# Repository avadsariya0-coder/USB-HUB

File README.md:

# USB HUB
Custom 4-port USB-C HUB
___________________________________________________________________________________________________________________________________________________________________________

## Overview

 USB HUB is a custom designed USB HUB and is built using the SL2.1A USB HUB controller and USB-C Connectors based on USB-2. The project is made using KICAD for schematic and PCB and Fusion 360 for the 3D designing.

Unlike the another readymade hubs this USB HUB is made from the scratch from designing schematic to the PCB routing to the 3D designing.

This HUB allows 1 USB-C connection to expand into 4 USB-C port. It is useful for connecting multiple devices to 1 device.

___________________________________________________________________________________________________________________________________________________________________________

## Inspiration

The inspiration for designing USB HUB with USB-C connectors comes from the lack of the ports in the laptop. Modern laptop comes with very few ports which makes difficult to connect to the multiple devices at once.While most of the readymade USB hub comes with the USB-A connectors which is not available in Modern Macbooks and another laptops. To solve that .To fix the issue I came up with the USB HUB containing 1X USB-C upstream port and 4X USB-C downstream port.

___________________________________________________________________________________________________________________________________________________________________________

## Features

• 1 USB-C upstream port

• 4 USB-C downstream ports

• SL2.1A USBHUB controller

• USB-C powered

• Lightweight and portable

_________________________________________________________________________________________________________________________________________________________________________

## Gallery

_________________________________________________________________________________________________________________________________________________________________________

## Hardware Stack

• SL2.1A UAB hub controller

• USB-C connectors

• Capacitors

• Resistors

• LED indicator

• Diode

_________________________________________________________________________________________________________________________________________________________________________

## Bill of material

[USB HUB BOM.csv](https://github.com/user-attachments/files/29343381/USB.HUB.BOM.csv)

_________________________________________________________________________________________________________________________________________________________________________

## Zine

_________________________________________________________________________________________________________________________________________________________________________

## PCB design

The PCB for USB HUB was designed using KICAD. PCB contains SL2.1A controller,USB-C connectors,Resistor,Capacitor,LED,Diode.

# Features

• USB-C connectivity

• Compact PCB

_________________________________________________________________________________________________________________________________________________________________________

## PCB

_________________________________________________________________________________________________________________________________________________________________________

## Schematic

_________________________________________________________________________________________________________________________________________________________________________

## Enclosure

The enclosure for USB HUB was designed using FUSION 360.

# Features

• USB-C port opening

• Compact form factor

_________________________________________________________________________________________________________________________________________________________________________

## Assembly guide

• Solder the SL2.1A USBHUB controller to the PCB

• Solder all capacitor and resistor.(NOTE: solder the component with correct values)

• Mount the USB-C connectors

• Install LED indicator

• Put the PCB inside the enclosure and add screws through the PCB mounting holes to the standoff pillars.

• Close the enclosure with the help of top lid

_________________________________________________________________________________________________________________________________________________________________________

## How to use

• Connect the USB-C input port to the host device

• Plug in another devices to the USB-C output plug

• Now,the USB HUB distributes the connection all the connected devices.

## Devices that can be used

• USB flash drive

• keyboards

• USB Card reader

• USB powered accesories.

## Uses 

• Used for trasferring data from 1 device to the multiple devices.

## Contributing

Contributions,suggestions, and feedback are welcome

If you'd like to improve USB HUB
1. Fork or clone the repository

https://github.com/avadsariya0-coder/USB-HUB

2. Create your Feature branch

3. Commit your changes

4. Open a pull request.

_________________________________________________________________________________________________________________________________________________________________________

## Creator

# Arman Vadsariya

17•India•Fallout

_________________________________________________________________________________________________________________________________________________________________________

## License

This project is licensed under MIT License.

_________________________________________________________________________________________________________________________________________________________________________

# USB HUB

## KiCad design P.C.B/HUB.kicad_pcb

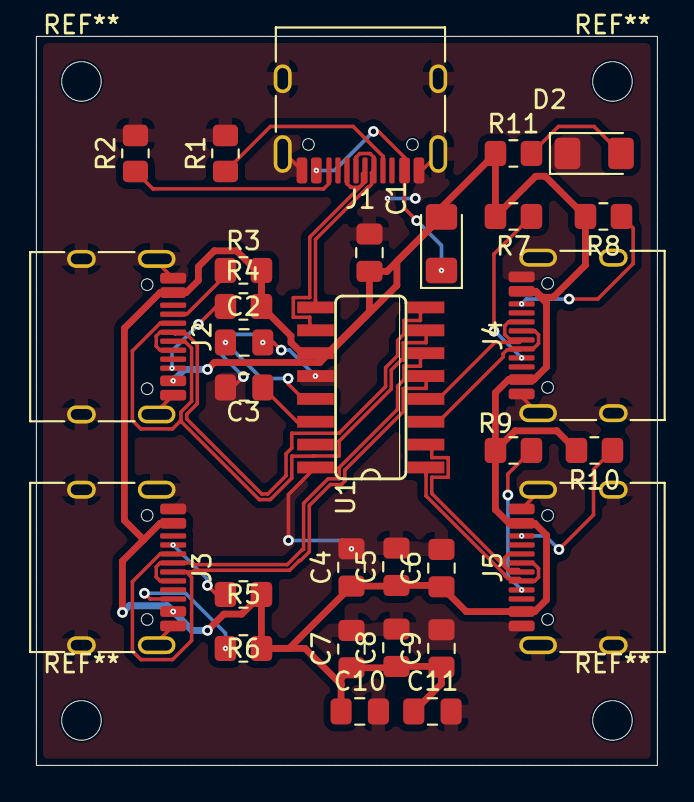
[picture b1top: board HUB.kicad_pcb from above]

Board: 2 copper layers, 34.5 x 40.5 mm, 30 parts (0 on the bottom side), 26 nets.

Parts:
C1, C5, C7, C9, C11: 100nF; C_0805_2012Metric_Pad1.18x1.45mm_HandSolder
C2, C3: 10uF; C_0805_2012Metric_Pad1.18x1.45mm_HandSolder
C4, C6, C8, C10: 1uF; C_0805_2012Metric_Pad1.18x1.45mm_HandSolder
D1: SD1206T020S1R0; D_1206_3216Metric_Pad1.42x1.75mm_HandSolder
D2: LED_Small; LED_1206_3216Metric_Pad1.42x1.75mm_HandSolder
J1, J2, J3, J4, J5: USB_C_Receptacle_USB2.0_16P; USB_C_Receptacle_HRO_TYPE-C-31-M-12
R1, R2: 5.1K; R_0805_2012Metric_Pad1.20x1.40mm_HandSolder
R3, R4, R5, R6, R7, R8, R9, R10: 56K; R_0805_2012Metric_Pad1.20x1.40mm_HandSolder
R11: 100; R_0805_2012Metric_Pad1.20x1.40mm_HandSolder
U1: SL2.1A; SO16

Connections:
/D1+: J2.A6 (D+), J2.B6 (D+), U1.8 (DP1)
/D1-: J2.A7 (D-), J2.B7 (D-), U1.7 (DM1)
/D2+: J3.A6 (D+), J3.B6 (D+), U1.6 (DP2)
/D2-: J3.A7 (D-), J3.B7 (D-), U1.5 (DM2)
/D3+: J4.A6 (D+), J4.B6 (D+), U1.4 (DP3)
/D3-: J4.A7 (D-), J4.B7 (D-), U1.3 (DM3)
/D4+: J5.A6 (D+), J5.B6 (D+), U1.2 (DP4)
/D4-: J5.A7 (D-), J5.B7 (D-), U1.1 (DM4)
/D+: J1.A6 (D+), J1.B6 (D+), U1.10 (DP)
/D-: J1.A7 (D-), J1.B7 (D-), U1.9 (DM)
/VBUS: C1.1, C4.1, C5.1, C6.1, C7.1, C8.1, C9.1, C10.1, C11.1, D1.2 (A), J2.A4 (VBUS), J2.A9 (VBUS), J2.B4 (VBUS), J2.B9 (VBUS), J3.A4 (VBUS), J3.A9 (VBUS), J3.B4 (VBUS), J3.B9 (VBUS), J4.A4 (VBUS), J4.A9 (VBUS), J4.B4 (VBUS), J4.B9 (VBUS), J5.A4 (VBUS), J5.A9 (VBUS), J5.B4 (VBUS), J5.B9 (VBUS), R3.2, R4.2, R5.2, R6.2, R7.2, R8.2, R9.2, R10.2, R11.1, U1.11 (VDD5)
GND: C1.2, C2.2, C3.2, C4.2, C5.2, C6.2, C7.2, C8.2, C9.2, C10.2, C11.2, D2.1 (K), J1.A1 (GND), J1.A12 (GND), J1.B1 (GND), J1.B12 (GND), J1.SH (SHIELD), J2.A1 (GND), J2.A12 (GND), J2.B1 (GND), J2.B12 (GND), J2.SH (SHIELD), J3.A1 (GND), J3.A12 (GND), J3.B1 (GND), J3.B12 (GND), J3.SH (SHIELD), J4.A1 (GND), J4.A12 (GND), J4.B1 (GND), J4.B12 (GND), J4.SH (SHIELD), J5.A1 (GND), J5.A12 (GND), J5.B1 (GND), J5.B12 (GND), J5.SH (SHIELD), R1.2, R2.2, U1.12 (GND), U1.16 (XIN)
unnamed: D1.1 (K), J1.A4 (VBUS), J1.A9 (VBUS), J1.B4 (VBUS), J1.B9 (VBUS)
unnamed: D2.2 (A), R11.2
unnamed: J1.A5 (CC1), R1.1
unnamed: J1.B5 (CC2), R2.1
unnamed: J2.A5 (CC1), R3.1
unnamed: J2.B5 (CC2), R4.1
unnamed: J3.A5 (CC1), R5.1
unnamed: J3.B5 (CC2), R6.1
unnamed: J4.A5 (CC1), R7.1
unnamed: J4.B5 (CC2), R8.1
unnamed: J5.A5 (CC1), R9.1
unnamed: J5.B5 (CC2), R10.1
unnamed: C3.1, U1.14 (VDD18)
unnamed: C2.1, U1.13 (VDD33)

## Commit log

2026-05-30 Create CAD
2026-05-31 Change header from H3 to H1 for USB HUB
2026-06-03 Add link to USB HUB BOM in README
